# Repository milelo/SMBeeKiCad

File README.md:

# SMBeeKiCad

Related GitHub projects:
* [SMBee Firmware] - The firmware source, build instructions and binaries.
* [SMBeeHive Programmer] - A low cost custom-jig and programmer for the SMBee.

# Manufacturing Data

It's fairly easy and inexpensive to have SMBee PCBs manufactured in low or high quantities. This is the information you need:

## Gerber files

The Gerber files defines the various layers that constitute a PCB design. The Gerber format is an open-standard 2D vector image format.

Generated gerber files for SMBee version:

| SMBee | Generated with KiCad | Download | Changes
-|-|-|- 
| 1.1.1 | 5.0.2-5-10.14 | [SMBee1.1.1.zip]
| 1.1.2 (latest)| 6.0.7 | [SMBee1.1.2.zip] | Add (solder) paste layers

Typically just send the zip to the manufacturer. The file formats and identifying file extensions will be accepted by most manufacturers including:

* [ELECROW]
* [PCBs.io]
* [AISLER]

See the [SMBee PCB costs] spreadsheet for more information on manufacturers.

## Manufacturing options

Some manufacturers have additional options that need to be specified:

Parameter | value |
-|-
Layers | 2 |
Thickness | 1.6mm |
Finish | Gold |
Copper weight | 1oz |
PCB colour | Black |
Dimensions | 57 x 43mm
Castellated holes | No

# BOM (Build Of Materials)

This is the [SMBee BOM] Spreadsheet for the parts. It includes suggested and alternate parts suppliers and their prices dependant on order quantity.

# Assembly instructions

See the [Project documentation](https://milelo.github.io/smbee).

# The Bee Schematic

Key features & operation:
1. U1 is a high performance, low power 8 bit microcontroller with 1k byte flash and 32 byte RAM. Refer to the [ATtiny10 data sheet] for detailed information.
1. Port B connections PB0, PB1 and PB2 have tri-state outputs: high, low, or high impedance. See table 1 for the LED states.
1. PB0 and PB1 are each configured in the firmware as a pulse-width-modulator output to enable control of the LED brightness.
1. Simultaneous illumination of LED combinations that require conflicting values of PB2, can be achieved by multiplexing the states. See table 1. This isn't supported by the current firmware.
1. The two eye LED's are connected in parallel and can't be individually controlled.
1. BT1 can only supply about 26mA short circuit. Its internal impedance limits the LED current, typically to a maximum of 6mA. This eliminates the need for a resistor to limit the current.
1. The specified LED's have been carefully selected for their relatively low volt-drop at the operating current, their high efficiency and thin construction. Substituting other types is unlikely to give good results.
1. The forward volt-drop of the LED's and U1 drive transistors ensure U1 has enough voltage to function even when the battery is running very low.
1. The circuit can be configured to draw < 200nA in sleep mode.
1. To allow PB3 to be used as an input, SMBee is intended to be programmed using the high voltage programming method. Applying 12V to PRG will enable external programming using the TPI protocol.
1. The default PB3 reset function can be disabled with the RSTDISBL (reset disable) fuse, and configured as an input with an internal pull-up. The firmware can configure the input and pull-up to remain active when the MCU is in sleep mode and generate a wake-up interrupt when the button is pressed.
1. SW1 must be de-bounced in firmware (10ms settle time).
1. During flash programming the two-LED volt-drop is sufficient to isolate the external signals CLK & DAT from each other.

The LED's are activated according to the following table:

Description | Active </BR> LED ID | PB2 | PB1 </BR> PWM-B | PB0 </BR> PWM-A
-|-|:-:|:-:|:-:
Antenna R | Dar1        | 0 | 1	| X
Antenna L | Dal1	    | 0	| X	| 1
Eyes      | Del1 & Der1 | 1	| 0	| X
Sting     | Dst1	    | 1	| X	| 0

**Table 1**, Key: **0:** output-low, **1:** output-high, **X:** don't care, **PB:** Port B, **PWM:** Pulse Width Modulator.

# View or edit the PCB design

The PCB was designed using KiCad EDA software. If you would like to view or edit the design files, download it from [KiCad download] and install the software. 

Clone this repository into your local file space and open SMBee.pro.

[ATtiny10 data sheet]: https://ww1.microchip.com/downloads/en/DeviceDoc/atmel-8127-avr-8-bit-microcontroller-attiny4-attiny5-attiny9-attiny10_datasheet.pdf
[GITHUB-LOCATION]: https://github.com/milelo/SMBeeKiCad
[SMBee Firmware]: https://github.com/milelo/SMBeeFirmware
[SMBeeHive Programmer]: https://github.com/milelo/SMBeeHiveKiCad
[SMBee1.1.1.zip]: https://github.com/milelo/SMBeeKiCad/blob/master/gerber/SMBee1.1.1.zip?raw=true
[SMBee1.1.2.zip]: https://github.com/milelo/SMBeeKiCad/blob/master/gerber/SMBee1.1.2.zip?raw=true
[ELECROW]: https://www.elecrow.com/pcb-manufacturing.html
[PCBs.io]: https://www.pcbs.io/
[AISLER]: https://aisler.net/
[SMBee PCB costs]: https://docs.google.com/spreadsheets/d/1pC-4M-7qa12mT0QL2S9FdDb4QyRmq4kYofQHElQal1s/edit#gid=567507746
[SMBee BOM]: https://docs.google.com/spreadsheets/d/1pC-4M-7qa12mT0QL2S9FdDb4QyRmq4kYofQHElQal1s/edit#gid=1645088434
[SMBee tools]: https://docs.google.com/spreadsheets/d/1pC-4M-7qa12mT0QL2S9FdDb4QyRmq4kYofQHElQal1s/edit#gid=802410893
[KiCad download]: http://kicad-pcb.org/download/

---

This work is Copyright © 2019 Mike Longworth

<br />This work is licensed under a <a rel="license" href="http://creativecommons.org/licenses/by/4.0/">Creative Commons Attribution 4.0 International License</a>.

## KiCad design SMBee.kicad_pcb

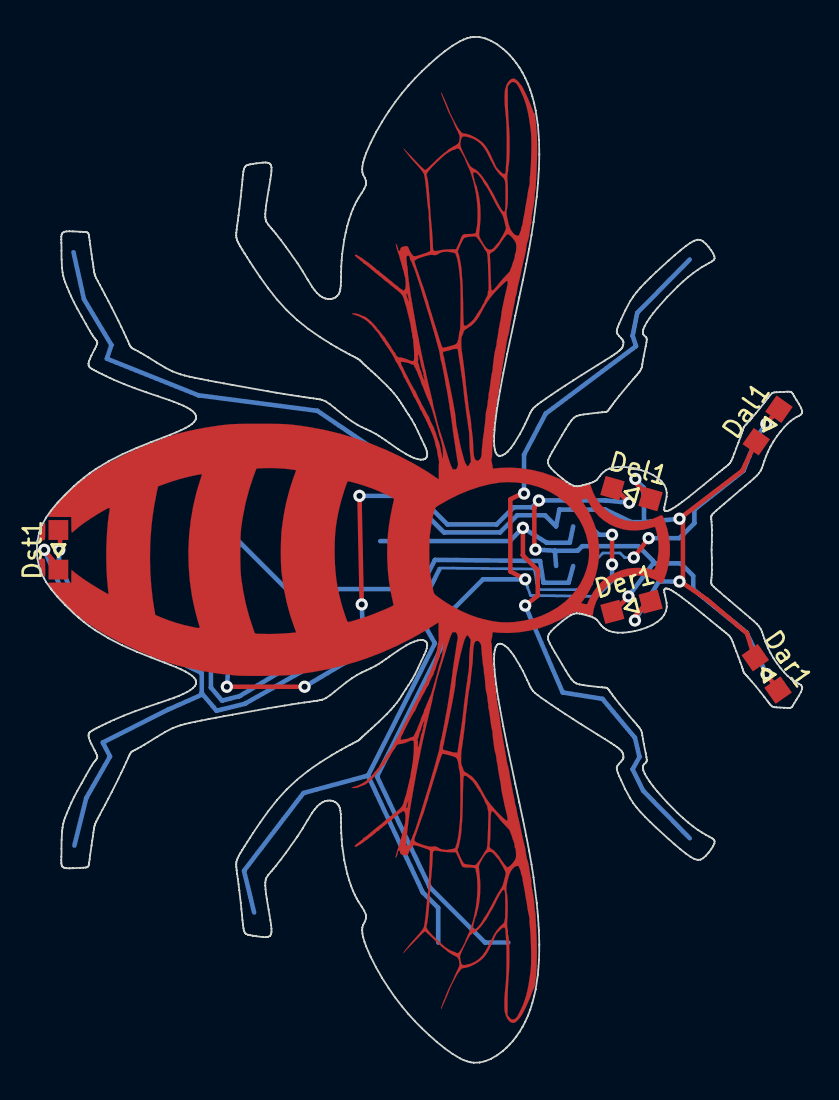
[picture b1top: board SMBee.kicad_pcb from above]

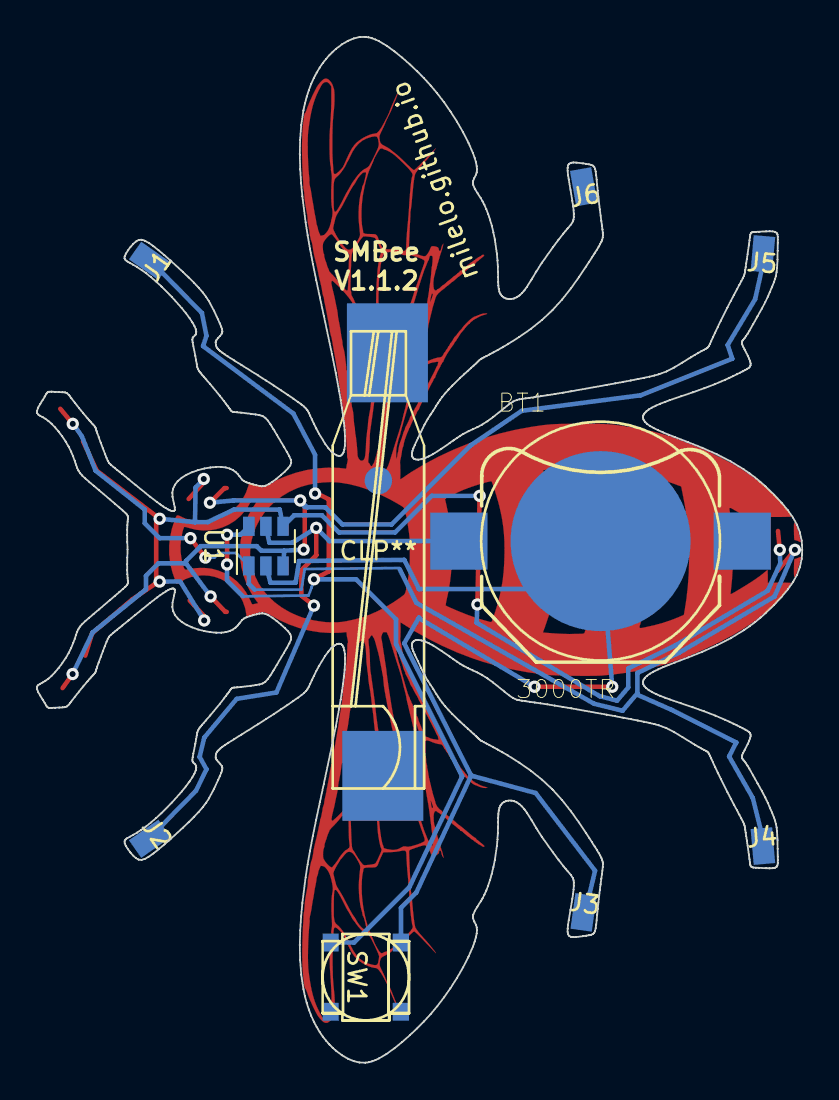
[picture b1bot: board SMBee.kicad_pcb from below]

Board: 2 copper layers, 42.5 x 57.0 mm, 17 parts (10 on the bottom side), 6 nets.

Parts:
BT1: 3000TR; BAT_3000TR
CLP**: Clasp1in
Dal1: LED; LED_0805
Dar1: LED; LED_0805
Del1: LED; LED_0805
Der1: LED; LED_0805
Dst1: LED; LED_0805
J1, J2, J3, J4, J5, J6: CONN_PIN; Conn-pad
SW1: ALPS_SKRB; ALPS-SKRB
U1: PIC10LF322-I/OT; SOT-23-6
W***: WING; WingCu
WF**: WINGF; WingFCu

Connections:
ICSPCLK: Dar1.2, Del1.1, Der1.1, J5.1, U1.3
ICSPDAT: Dal1.2, Dst1.1, J4.1, U1.1
unnamed: Dal1.1, Dar1.1, Del1.2, Der1.2, Dst1.2, U1.4
Vdd: BT1.1, J2.1, U1.5
Vpp: J1.1, SW1.2, U1.6
Vss: BT1.2, J3.1, SW1.1, U1.2

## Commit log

2019-03-08 SMBee1.1 files migrated to KiCad 5
2019-05-30 add doc svgs
2019-08-05 KiCad 5.02-5-10.14 gerber
2019-08-27 Rotate 180º
2019-08-27 Updated pins to match SMBeeHive
2019-08-27 Rename connector and signals to match SMBeeHive
2019-08-27 Development updates
2019-08-27 Fix PCB options table
2019-09-03 Dev updates
2019-09-30 License
2019-10-01 Minor updates
2022-09-05 1.1.1 > 1.1.2 Migrate to kicad 6 Add (solder) paste layers Minor DRC fixes
2022-09-05 Add solder paste layers
    Migrate to KiCad 6.
    Add solder paste layers
    Minor DRC fixes
2022-09-05 Add release changes
